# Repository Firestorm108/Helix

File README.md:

# Helix

An automatic coil winding machine for high voltage transformers, electromagnetics, motors, etc. The combination of the leadscrew controlled spool holder and aligning/tensioning system with the precise TMC2209 controlled stepper spinner ensures even winding across every layer.
The device aims to reduce long hours spent hand winding crappy transformers so that prototyping is quick and efficient. The all-in-one control board has integrated stepper drivers and hooks up to the LCD/rotary encoder based control panel. 
It is easily reprogrammable with USB-C. With a small <75mmx75mm footprint, it fits nicely into the enclosure.

Demo Video: https://youtube.com/shorts/A1r3ZOApkCI?si=vdlbSpJHiryxB_zt

## Main Features 

- Automatic alignment
- Software defined sensing
- High speeds and precision
- Easy reprogrammability + control panel
- Small, portable design
- Custom control board
- Anti-overlap protection

# Pictures

# Helix BOM
*You can find the spreadsheet version here: https://docs.google.com/spreadsheets/d/1YcLF46WpMoUjMdwvhuiZ--BbrOf5m03kofhXg6CQ6rc/edit?usp=sharing

## Electronics

| Item                                           |  Cost |
| ---------------------------------------------- | ----: |
| JLCPCB + Assembly (2 PCBs)                     |   $80 |
| Pin Headers                                    | $3.00 |
| 2x1 Screw Terminals                            |    $3 |
| DC Barrel Jack                                 |    $2 |
| White LCD w/ I2C                               |    $4 |
| Rotary Encoder                                 |    $4 |
| 3× TMC2209 Drivers                             |    $9 |
| 2× Stepper Motors                              |   $12 |
| 24V 5A Power Supply                            |   $13 |
| USB-C Power Transfer Board                     |    $2 |
| LM7805 Voltage Regulator                       |    $2 |
| Backup Devboard *(in case of PCB failure)*     |    $3 |
| Backup 5V Regulator *(in case of PCB failure)* |    $3 |
| 330µF 35V Capacitor                            |    $3 |
| Jumpers                                        |    $4 |

## Hardware

| Item                                   | Cost |
| -------------------------------------- | ---: |
| M3 Standoffs (10 mm)                   |   $2 |
| M2 Standoffs (6 mm)                    |   $2 |
| 8 mm M3 Screws                         |   $1 |
| 8 mm M2 Screws                         |   $1 |
| TO-220 Heatsink                        |   $2 |
| 300 mm 2020 Aluminum Extrusions        |  $14 |
| 150 mm 2020 Aluminum Extrusions        |  $19 |
| Corner Brackets                        |  $20 |
| 5 mm → 8 mm Couplers (2×)              |   $5 |
| 250 mm 8 mm Rod                        |   $5 |
| 608 Bearings                           |   $7 |
| 250 mm T8 (2 mm Lead) Leadscrew w/ Nut |   $9 |
| M5 20 mm Thumbscrew                    |   $3 |
| 1 mm × 8 mm Spring                     |   $4 |

## Cost Summary

| Category    |     Cost |
| ----------- | -------: |
| Electronics |     $147 |
| Hardware    |      $94 |
| **Total**   | **$241** |

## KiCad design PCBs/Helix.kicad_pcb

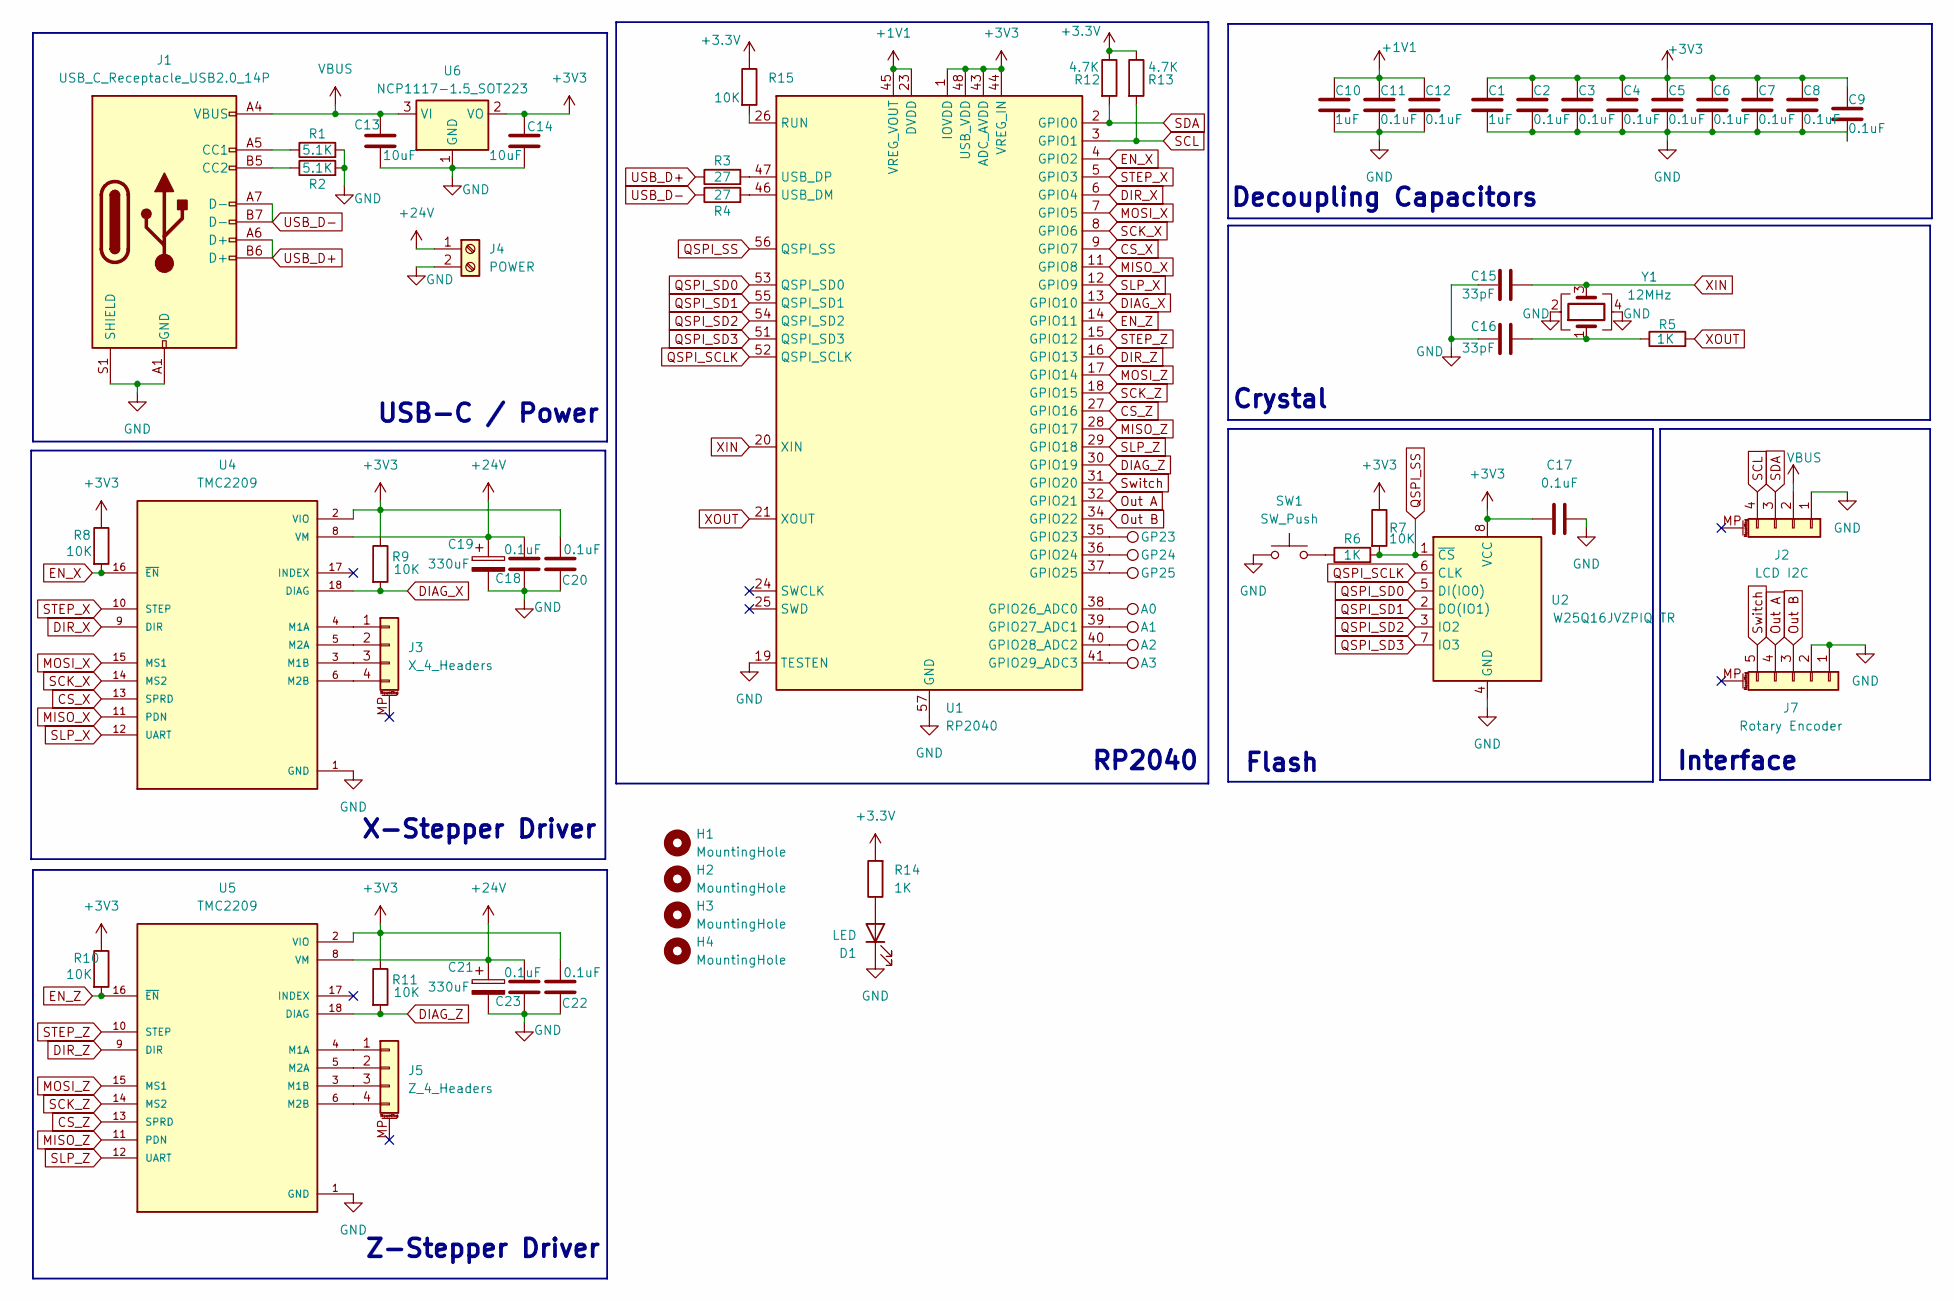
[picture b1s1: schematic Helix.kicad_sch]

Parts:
A0, A1, A2, A3: TestPoint; TestPoint_Plated_Hole_D2.0mm
C1, C10: 1uF; C_0402_1005Metric
C2, C3, C4, C5, C6, C7, C8, C9, C11, C12, C17, C18, C20, C22, C23: 0.1uF; C_0402_1005Metric
C13, C14: 10uF; C_0603_1608Metric
C15, C16: 33pF; C_0402_1005Metric
C19, C21: 330uF; CP_Radial_D10.0mm_P5.00mm
D1: LED; LED_0402_1005Metric
GP23, GP24, GP25: TestPoint; TestPoint_Plated_Hole_D2.0mm
H1, H2, H3, H4: MountingHole; MountingHole_3.2mm_M3
J1: USB_C_Receptacle_USB2.0_14P; USB_C_Receptacle_HRO_TYPE-C-31-M-12
J2: LCD I2C; PinHeader_1x04_P2.54mm_Vertical
J3: X_4_Headers; PinHeader_1x04_P2.54mm_Vertical
J4: POWER; PinHeader_1x02_P2.54mm_Vertical
J5: Z_4_Headers; PinHeader_1x04_P2.54mm_Vertical
J7: Rotary Encoder; PinHeader_1x05_P2.54mm_Vertical
R1, R2: 5.1K; R_0402_1005Metric
R3, R4: 27; R_0402_1005Metric
R5, R6, R14: 1K; R_0402_1005Metric
R7, R8, R9, R10, R11, R15: 10K; R_0402_1005Metric
R12, R13: 4.7K; R_0402_1005Metric
SW1: SW_Push; SW_Push_SPST_NO_Alps_SKRK
U1: RP2040; QFN-56-1EP_7x7mm_P0.4mm_EP3.2x3.2mm
U2: W25Q16JVZPIQ TR; Winbond_USON-8-1EP_3x2mm_P0.5mm_EP0.2x1.6mm
U4, U5: TMC2209; MODULE_TMC2209_SILENTSTEPSTICK; PARTREV 1.20
U6: NCP1117-1.5_SOT223; SOT-223-3_TabPin2
Y1: 12MHz; Crystal_SMD_3225-4Pin_3.2x2.5mm

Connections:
+1V1: C10.1, C11.1, C12.1, U1.23 (DVDD), U1.45 (VREG_VOUT), U1.50 (DVDD)
+3.3V: R12.1, R13.1, R14.2, R15.1
+3V3: C1.1, C2.1, C3.1, C4.1, C5.1, C6.1, C7.1, C8.1, C9.1, C14.1, C17.1, C18.2, C23.2, R7.1, R8.1, R9.1, R10.1, R11.1, U1.1 (IOVDD), U1.10 (IOVDD), U1.22 (IOVDD), U1.33 (IOVDD), U1.42 (IOVDD), U1.43 (ADC_AVDD), U1.44 (VREG_IN), U1.48 (USB_VDD), U1.49 (IOVDD), U2.8 (VCC), U4.2 (VIO), U5.2 (VIO), U6.2 (VO)
+24V: C19.1, C20.2, C21.1, C22.2, J4.1, U4.8 (VM), U5.8 (VM)
CS_X: U1.9 (GPIO7), U4.13 (SPRD)
CS_Z: U1.27 (GPIO16), U5.13 (SPRD)
DIAG_X: R9.2, U1.13 (GPIO10), U4.18 (DIAG)
DIAG_Z: R11.2, U1.30 (GPIO19), U5.18 (DIAG)
DIR_X: U1.6 (GPIO4), U4.9 (DIR)
DIR_Z: U1.16 (GPIO13), U5.9 (DIR)
EN_X: R8.2, U1.4 (GPIO2), U4.16 (~EN)
EN_Z: R10.2, U1.14 (GPIO11), U5.16 (~EN)
GND: C1.2, C2.2, C3.2, C4.2, C5.2, C6.2, C7.2, C8.2, C9.2, C10.2, C11.2, C12.2, C13.2, C14.2, C15.1, C16.1, C17.2, C18.1, C19.2, C20.1, C21.2, C22.1, C23.1, D1.1 (K), J1.A1 (GND), J1.A12 (GND), J1.B1 (GND), J1.B12 (GND), J1.S1 (SHIELD), J2.1, J4.2, J7.1, J7.2, R1.2, R2.2, SW1.1, U1.19 (TESTEN), U1.57 (GND), U2.4 (GND), U4.1 (GND), U4.7 (GND), U5.1 (GND), U5.7 (GND), U6.1 (GND), Y1.2, Y1.4
MISO_X: U1.11 (GPIO8), U4.11 (PDN)
MISO_Z: U1.28 (GPIO17), U5.11 (PDN)
MOSI_X: U1.7 (GPIO5), U4.15 (MS1)
MOSI_Z: U1.17 (GPIO14), U5.15 (MS1)
unnamed: C16.2, R5.1, Y1.1
unnamed: D1.2 (A), R14.1
unnamed: J1.A5 (CC1), R1.1
unnamed: J1.B5 (CC2), R2.1
unnamed: J3.1, U4.4 (M1A)
unnamed: J3.2, U4.5 (M2A)
unnamed: J3.3, U4.3 (M1B)
unnamed: J3.4, U4.6 (M2B)
unnamed: J5.1, U5.4 (M1A)
unnamed: J5.2, U5.5 (M2A)
unnamed: J5.3, U5.3 (M1B)
unnamed: J5.4, U5.6 (M2B)
unnamed: R6.1, SW1.2
unnamed: GP23.1, U1.35 (GPIO23)
unnamed: GP24.1, U1.36 (GPIO24)
unnamed: GP25.1, U1.37 (GPIO25)
unnamed: A0.1, U1.38 (GPIO26_ADC0)
unnamed: A1.1, U1.39 (GPIO27_ADC1)
unnamed: A2.1, U1.40 (GPIO28_ADC2)
unnamed: A3.1, U1.41 (GPIO29_ADC3)
unnamed: R15.2, U1.26 (RUN)
unnamed: R4.2, U1.46 (USB_DM)
unnamed: R3.2, U1.47 (USB_DP)
Out A: J7.4, U1.32 (GPIO21)
Out B: J7.3, U1.34 (GPIO22)
QSPI_SCLK: U1.52 (QSPI_SCLK), U2.6 (CLK)
QSPI_SD0: U1.53 (QSPI_SD0), U2.5 (DI(IO0))
QSPI_SD1: U1.55 (QSPI_SD1), U2.2 (DO(IO1))
QSPI_SD2: U1.54 (QSPI_SD2), U2.3 (IO2)
QSPI_SD3: U1.51 (QSPI_SD3), U2.7 (IO3)
QSPI_SS: R6.2, R7.2, U1.56 (QSPI_SS), U2.1 (~CS)
SCK_X: U1.8 (GPIO6), U4.14 (MS2)
SCK_Z: U1.18 (GPIO15), U5.14 (MS2)
SCL: J2.4, R13.2, U1.3 (GPIO1)
SDA: J2.3, R12.2, U1.2 (GPIO0)
SLP_X: U1.12 (GPIO9), U4.12 (UART)
SLP_Z: U1.29 (GPIO18), U5.12 (UART)
STEP_X: U1.5 (GPIO3), U4.10 (STEP)
STEP_Z: U1.15 (GPIO12), U5.10 (STEP)
Switch: J7.5, U1.31 (GPIO20)
USB_D+: J1.A6 (D+), J1.B6 (D+), R3.1
USB_D-: J1.A7 (D-), J1.B7 (D-), R4.1
VBUS: C13.1, J1.A4 (VBUS), J1.A9 (VBUS), J1.B4 (VBUS), J1.B9 (VBUS), J2.2, U6.3 (VI)
XIN: C15.2, U1.20 (XIN), Y1.3
XOUT: R5.2, U1.21 (XOUT)

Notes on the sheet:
RP2040
USB-C / Power
Crystal
Interface
Decoupling Capacitors
Flash
Z-Stepper Driver
X-Stepper Driver

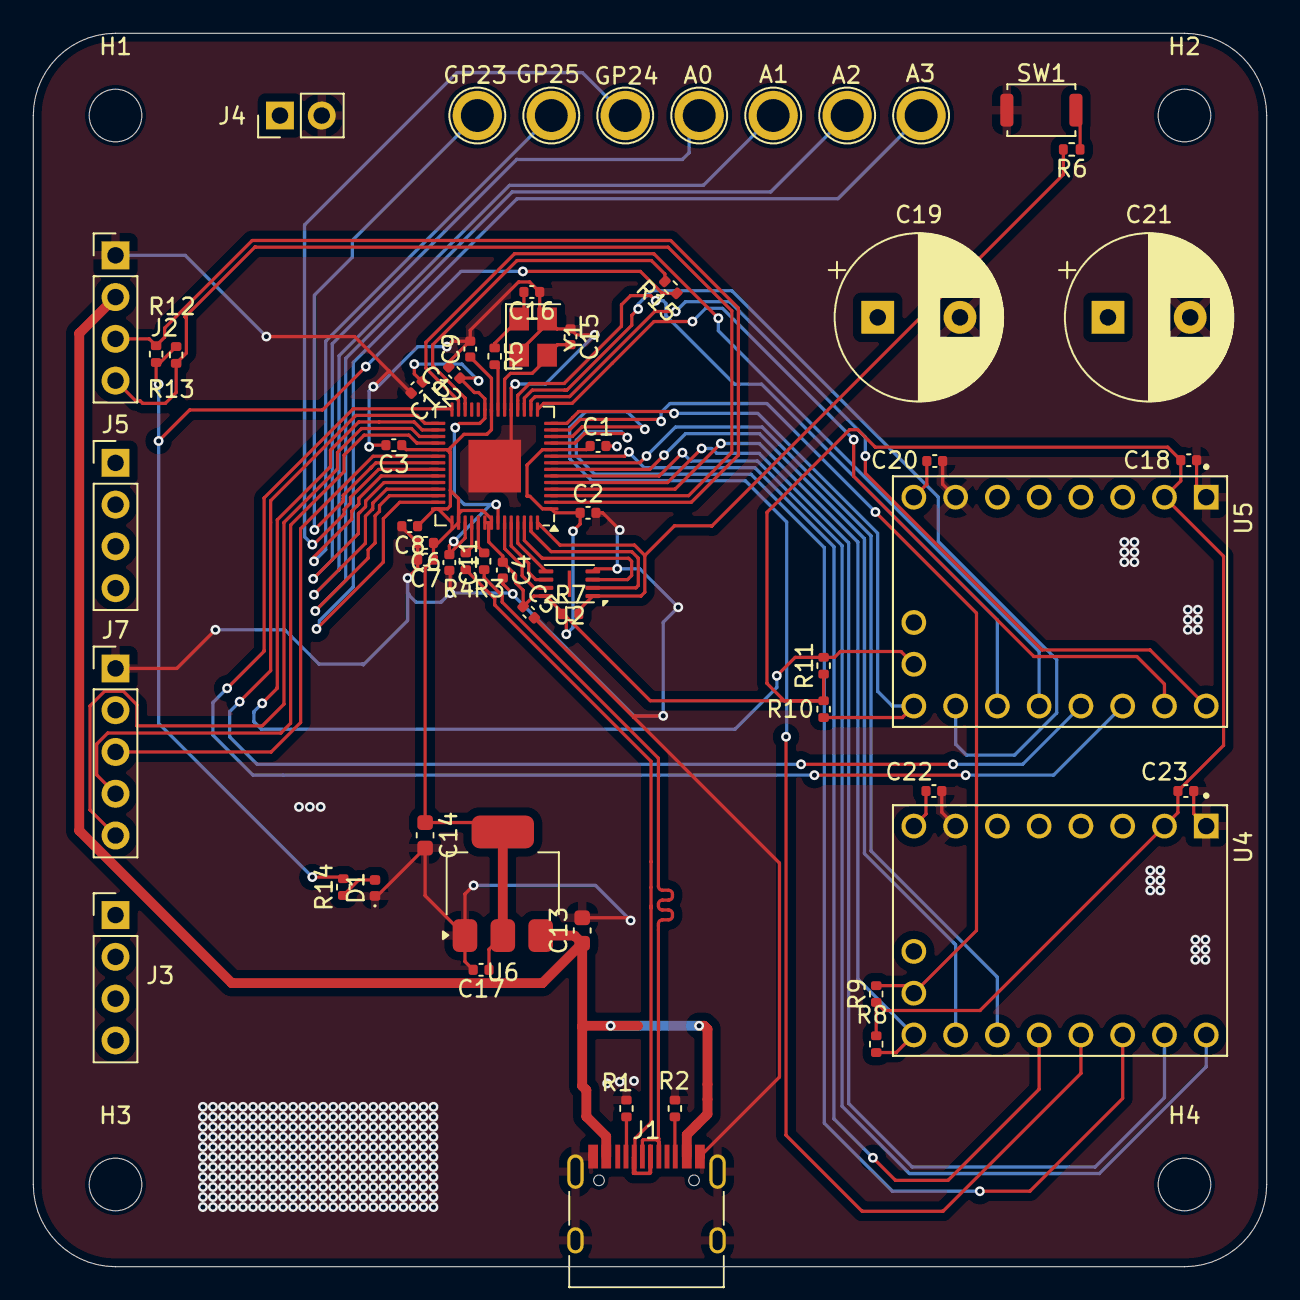
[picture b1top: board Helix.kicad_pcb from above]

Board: 4 copper layers, 75.0 x 75.0 mm, 63 parts (0 on the bottom side), 62 nets.

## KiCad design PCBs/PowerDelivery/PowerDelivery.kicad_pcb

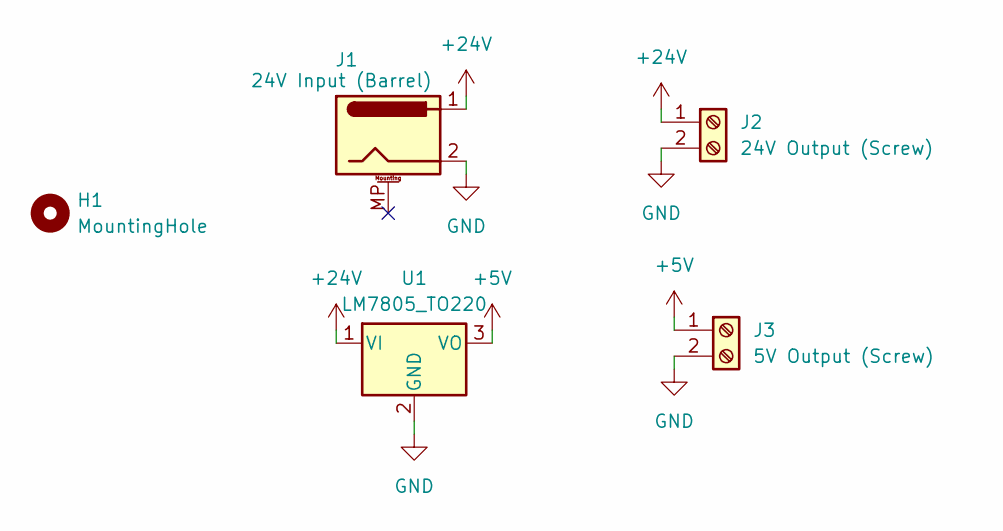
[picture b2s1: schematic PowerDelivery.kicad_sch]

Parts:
H1: MountingHole; MountingHole_3.2mm_M3
J1: 24V Input (Barrel); BarrelJack_CUI_PJ-102AH_Horizontal
J2: 24V Output (Screw); PinHeader_1x02_P2.54mm_Vertical
J3: 5V Output (Screw); PinHeader_1x02_P2.54mm_Vertical
U1: LM7805_TO220; TO-220-3_Vertical

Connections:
+5V: J3.1, U1.3 (VO)
+24V: J1.1, J2.1, U1.1 (VI)
GND: J1.2, J2.2, J3.2, U1.2 (GND)

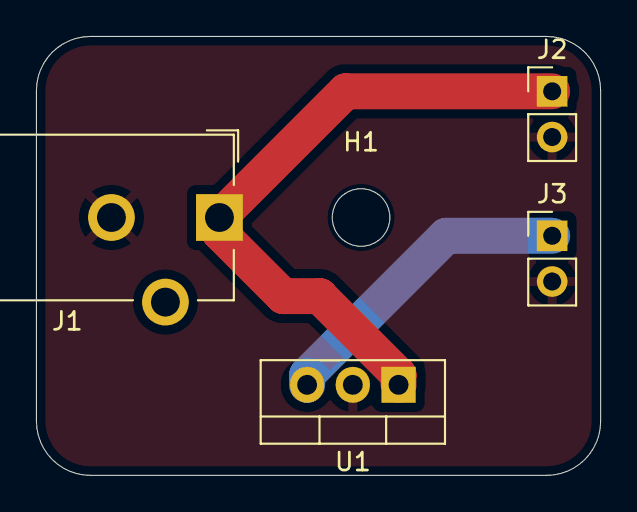
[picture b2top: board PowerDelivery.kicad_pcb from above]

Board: 2 copper layers, 31.3 x 24.4 mm, 5 parts (0 on the bottom side), 3 nets.

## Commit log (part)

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2026-01-11 Add temporary BOM for tracking items
2026-01-14 Add coupler to BOM with link
2026-06-06 Document spooling system mechanics in journal
    Added a new entry detailing the completion of the spooling system and its mechanics.
2026-06-07 PCBs
